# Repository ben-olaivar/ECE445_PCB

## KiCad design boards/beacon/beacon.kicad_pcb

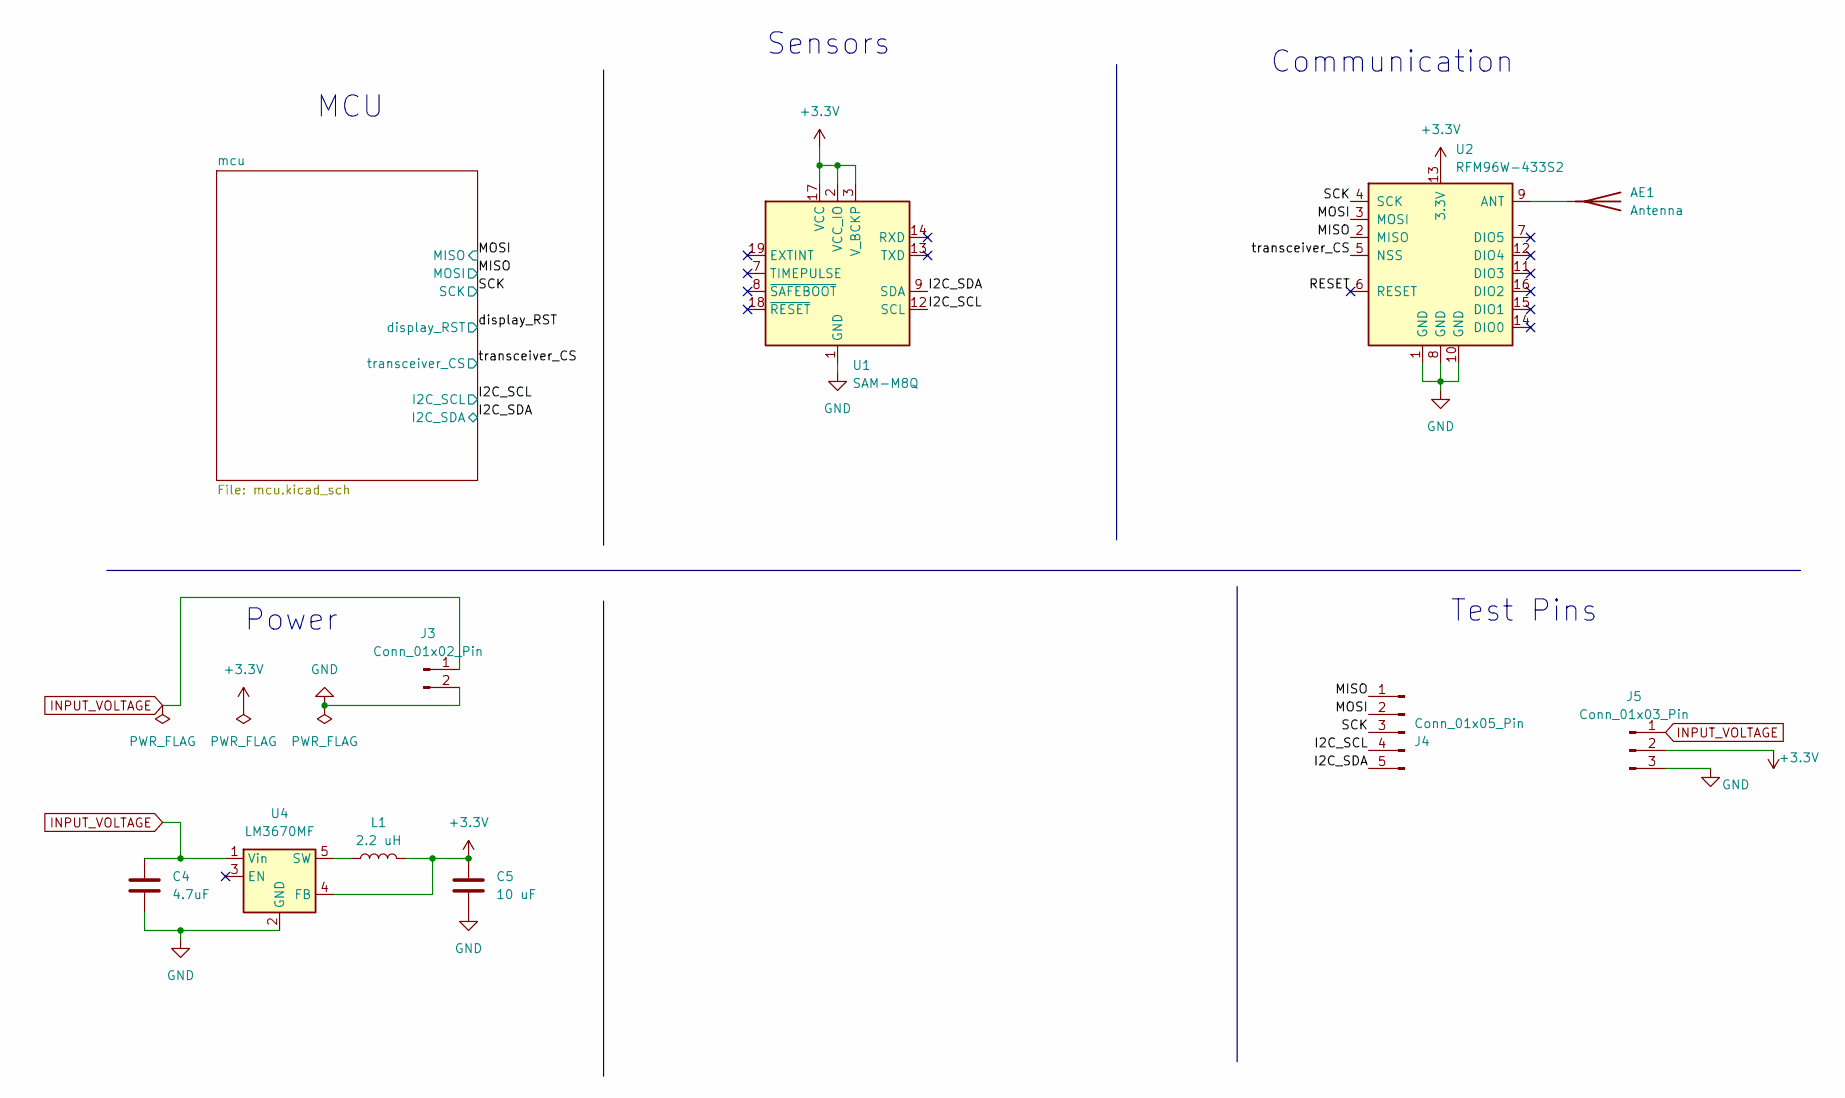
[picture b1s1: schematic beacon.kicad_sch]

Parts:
AE1: Antenna; SMA_Amphenol_901-143_Horizontal
C4: 4.7uF; C_0805_2012Metric
C5: 10 uF; C_0805_2012Metric
J3: Conn_01x02_Pin; PinHeader_1x02_P2.54mm_Vertical
J4: Conn_01x05_Pin; PinHeader_1x05_P2.54mm_Vertical
J5: Conn_01x03_Pin; PinHeader_1x03_P2.54mm_Vertical
L1: 2.2 uH; L_0805_2012Metric
U1: SAM-M8Q; ublox_SAM-M8Q
U2: RFM96W-433S2; HOPERF_RFM9XW_THT
U4: LM3670MF; TSOT-23-5

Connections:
+3.3V: C5.1, J5.2, L1.2, U1.2 (VCC_IO), U1.3 (V_BCKP), U1.17 (VCC), U2.13 (3.3V), U4.4 (FB); also elsewhere on the board
/I2C_SCL: J4.4, U1.12 (SCL); also elsewhere on the board
/I2C_SDA: J4.5, U1.9 (SDA); also elsewhere on the board
/MISO: J4.1, U2.2 (MISO); also elsewhere on the board
/MOSI: J4.2, U2.3 (MOSI); also elsewhere on the board
/RESET: U2.6 (RESET)
/SCK: J4.3, U2.4 (SCK); also elsewhere on the board
/transceiver_CS: U2.5 (NSS); also elsewhere on the board
GND: C4.2, C5.2, J3.2, J5.3, U1.1 (GND), U1.4 (GND), U1.5 (GND), U1.6 (GND), U1.10 (GND), U1.11 (GND), U1.15 (GND), U1.16 (GND), U1.20 (GND), U2.1 (GND), U2.8 (GND), U2.10 (GND), U4.2 (GND); also elsewhere on the board
INPUT_VOLTAGE: C4.1, J3.1, J5.1, U4.1 (Vin)
unnamed: AE1.1 (A), U2.9 (ANT)
unnamed: L1.1, U4.5 (SW)

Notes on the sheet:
MCU
Test Pins
Sensors
Communication
Power

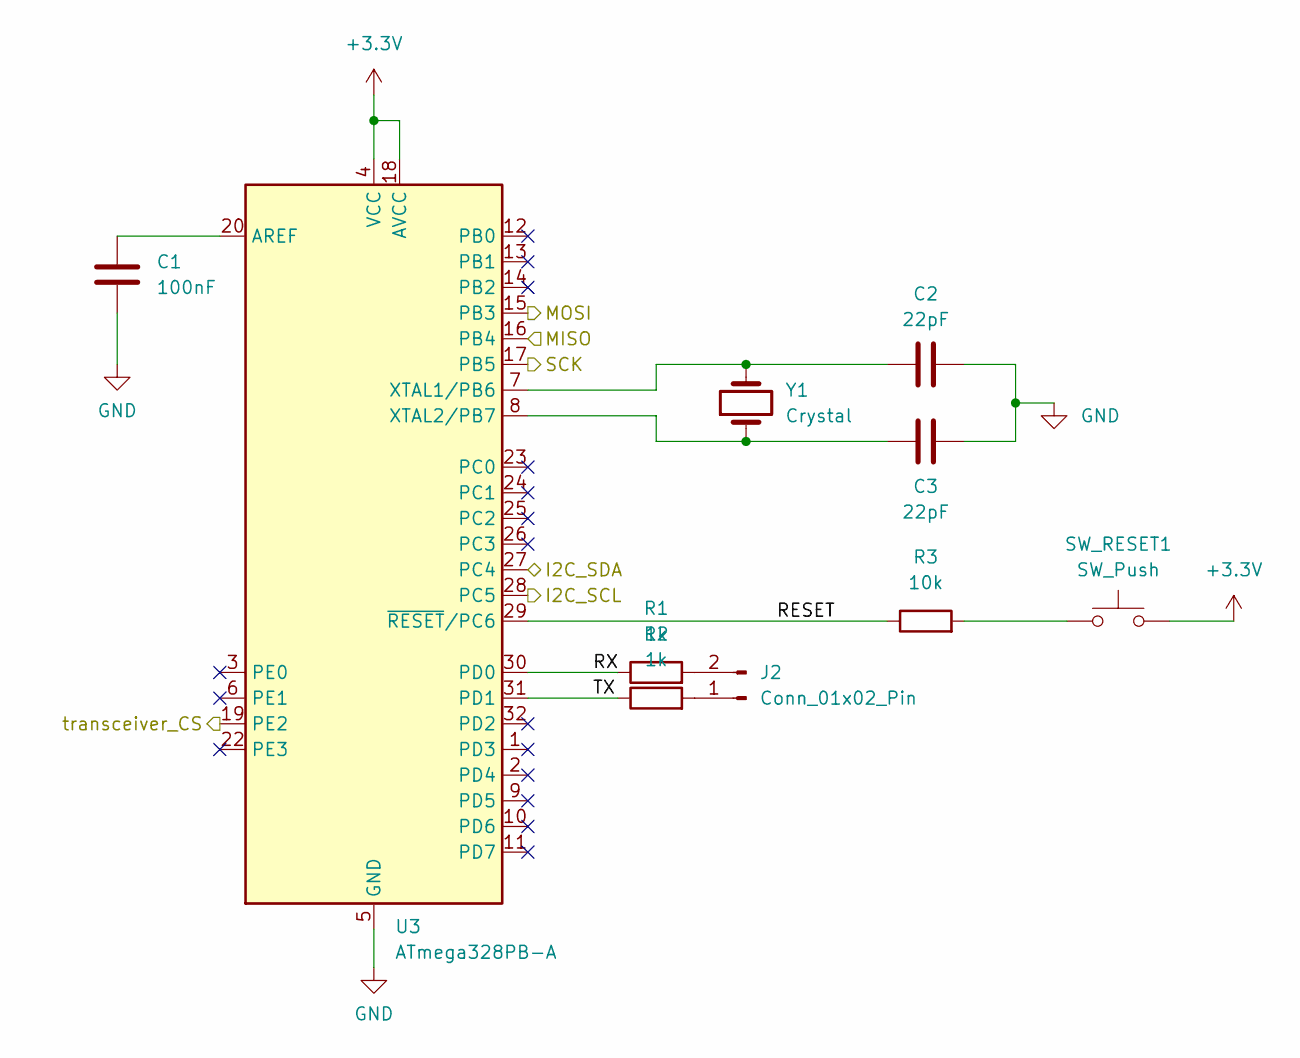
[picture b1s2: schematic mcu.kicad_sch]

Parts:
C1: 100nF; C_0805_2012Metric
C2, C3: 22pF; C_0805_2012Metric
J2: Conn_01x02_Pin; PinHeader_1x02_P2.54mm_Vertical
R1, R2: 1k; R_0805_2012Metric
R3: 10k; R_0805_2012Metric
SW_RESET1: SW_Push; SW_SPST_PTS645
U3: ATmega328PB-A; TQFP-32_7x7mm_P0.8mm
Y1: Crystal; XTAL_ABLS-16_ABR

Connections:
+3.3V: SW_RESET1.1, U3.4 (VCC), U3.18 (AVCC); also elsewhere on the board
/I2C_SCL: U3.28 (PC5); also elsewhere on the board
/I2C_SDA: U3.27 (PC4); also elsewhere on the board
/MISO: U3.15 (PB3); also elsewhere on the board
/MOSI: U3.16 (PB4); also elsewhere on the board
/SCK: U3.17 (PB5); also elsewhere on the board
/mcu/RESET: R3.1, U3.29 (~RESET/PC6)
/mcu/RX: R1.1, U3.30 (PD0)
/mcu/TX: R2.1, U3.31 (PD1)
/transceiver_CS: U3.19 (PE2); also elsewhere on the board
GND: C1.1, C2.2, C3.2, U3.5 (GND), U3.21 (GND); also elsewhere on the board
unnamed: J2.1, R2.2
unnamed: J2.2, R1.2
unnamed: R3.2, SW_RESET1.2
unnamed: C1.2, U3.20 (AREF)
unnamed: C2.1, U3.7 (XTAL1/PB6), Y1.2
unnamed: C3.1, U3.8 (XTAL2/PB7), Y1.1

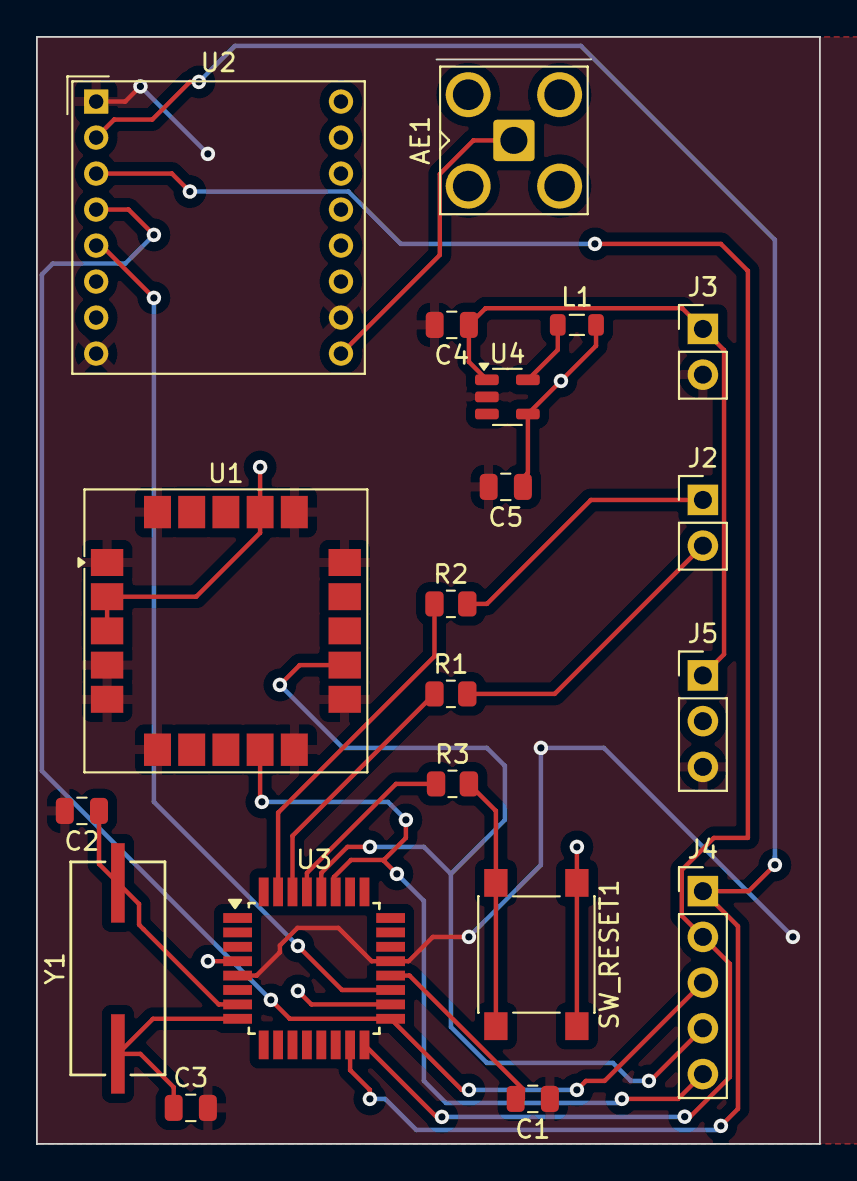
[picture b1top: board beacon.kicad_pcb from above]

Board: 2 copper layers, 43.5 x 61.5 mm, 20 parts (0 on the bottom side), 20 nets.

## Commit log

2024-02-14 inital push
2024-02-14 add relevant folders
2024-02-17 Add files via upload
    SAM-M8Q models
2024-02-17 Add files via upload
    ATMega files
2024-02-17 Add files via upload
    LoRa module model
2024-02-29 simple schematic format layout
2024-02-29 created section for test pins
2024-02-29 added notes
2024-03-01 Add files via upload
    Possible screen lib
2024-03-01 added sensor and MCU
2024-03-02 added manas hanheld tracker edits
2024-03-02 added test pads, UI buttons, and routed MCU pins
2024-03-03 buck placed on sch
2024-03-04 added gitignore to remove backups and personal settings
2024-03-04 added all footprints and modified gitignore
2024-03-04 basic pcb layout
2024-03-04 added traces for buttons
2024-03-04 cleanup and trace work
2024-03-04 almost all stuff added and traced, just need proper 3.3 and GND planes plus the mounting holes I think
2024-03-04 ignoring mounting holes for now
2024-03-05 changed push buttons' 3v to ground, added conn component to power supply
2024-03-05 finished board pre-review
2024-03-05 board traces pre-review
2024-03-30 finished beacon schematic
2024-04-02 pcb organization done for now, tracing asap
2024-04-02 some starter traces
2024-04-02 beacon down to warnings only
